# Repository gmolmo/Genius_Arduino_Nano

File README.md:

<h1 align="center"> 🔵🟢 Genius / Simon - Arduino 🟡🔴 </h1>

<div align="center">

</div>

## Descrição do Projeto
O projeto consiste no desenvolvimento do clássico jogo de memória **Genius (ou Simon)** utilizando um **Arduino Nano**. O objetivo do jogo é memorizar e repetir a sequência aleatória de luzes e sons apresentada pelos LEDs e buzzer. É possível selecionar a quantidade de rodadas desejadas e, com o avançar do jogo, o tempo de exibição é diminuído para aumentar a dificuldade.

O desenvolvimento passou pelas etapas de prototipagem em protoboard, soldagem final dos componentes em uma placa perfurada e montagem em um case feito em impressão 3D (feito por membros antigos da **ERUS UFES**).
<div align="center">
  
</div>

## ⚙️ Funcionamento

### Software
O código foi inteiramente programado em **C++** modularizado sob o conceito de **TAD (Tipo Abstrato de Dados)**. A estrutura foi dividida em três arquivos principais:
- `Genius.h`: Contém a definição da classe `Genius`, protótipos de métodos e atributos.
- `Genius.cpp`: Implementação da lógica do jogo, controle de som via buzzer, animações de LEDs (Início, Vitória e Game Over), gerenciamento de estados e leitura dos botões.
- `main.cpp`: Executa o setup e o loop principal com a máquina de estados do jogo.

O programa conta com **3 níveis de dificuldade** selecionáveis pelo botão de controle antes do início da partida, indicados por LEDs dedicados.

### Hardware
- **Arduino Nano**: Microcontrolador responsável pelo processamento da lógica.
- **LEDs Coloridos**: 4 LEDs para a sequência do jogo e 3 LEDs para indicação do nível de dificuldade.
- **Push Buttons**: 4 botões para entrada do jogador e 1 botão para seleção de dificuldade.
- **Buzzer Passivo**: Emite tons em frequências específicas para cada LED e reproduz os efeitos sonoros do jogo.
- **Placa Perfurada**: Circuito soldado para garantir durabilidade e conexões firmes.
- **Case 3D**: Case plástico impresso em 3D para abrigar a eletrônica.

## 🪚 Ferramentas

### C++ / Arduino Framework 
Linguagem utilizada no desenvolvimento de toda a lógica do projeto, aplicando orientação a objetos básica e boa organização estrutural.

### PlatformIO (VS Code)  
Ecossistema utilizado para compilação, gerenciamento de dependências e upload do código diretamente para o Arduino Nano através do Visual Studio Code.

## Instruções

Para compilar e enviar o projeto para o Arduino:

1. Certifique-se de ter o **VS Code** instalado com a extensão do **PlatformIO**.
2. Clone o repositório ou baixe o pacote completo de código.
3. Abra a pasta do projeto no VS Code.
4. Conecte o **Arduino Nano** à porta USB do seu computador.
5. Acesse a aba do **PlatformIO** na barra lateral e clique em **Upload** (ou utilize o atalho do VS Code).

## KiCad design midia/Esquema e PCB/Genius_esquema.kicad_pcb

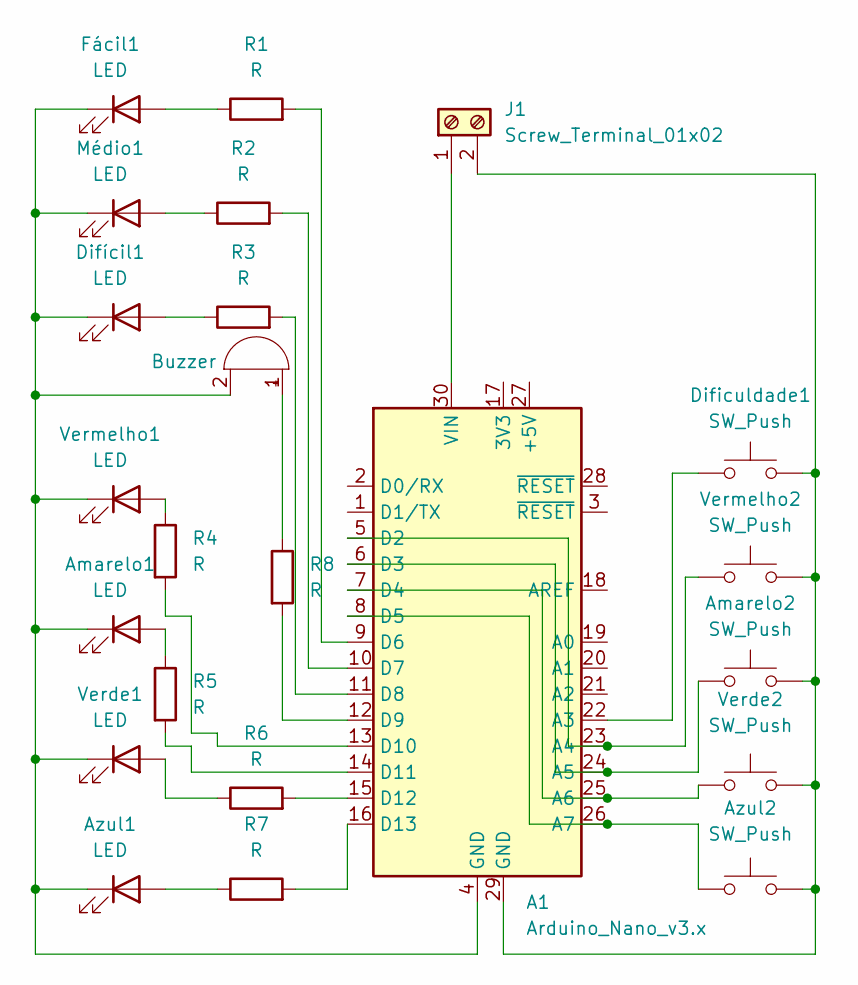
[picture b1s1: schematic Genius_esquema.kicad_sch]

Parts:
A1: Arduino_Nano_v3.x; Arduino_Nano
Amarelo1: LED; LED_D5.0mm
Amarelo2: SW_Push; PinHeader_1x02_P2.54mm_Vertical
Azul1: LED; LED_D5.0mm
Azul2: SW_Push; PinHeader_1x02_P2.54mm_Vertical
BZ1: Buzzer; Buzzer_12x9.5RM7.6
Dificuldade1: SW_Push; PinHeader_1x02_P2.54mm_Vertical
Difícil1: LED; LED_D5.0mm
Fácil1: LED; LED_D5.0mm
J1: Screw_Terminal_01x02; TerminalBlock_Phoenix_MKDS-1,5-2-5.08_1x02_P5.08mm_Horizont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
Médio1: LED; LED_D5.0mm
R1, R2, R3, R4, R5, R6, R7, R8: R; R_Axial_DIN0207_L6.3mm_D2.5mm_P7.62mm_Horizontal
Verde1: LED; LED_D5.0mm
Verde2: SW_Push; PinHeader_1x02_P2.54mm_Vertical
Vermelho1: LED; LED_D5.0mm
Vermelho2: SW_Push; PinHeader_1x02_P2.54mm_Vertical

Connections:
unnamed: A1.22 (A3), Dificuldade1.1
unnamed: A1.5 (D2), A1.23 (A4), Vermelho2.1
unnamed: A1.6 (D3), A1.24 (A5), Amarelo2.1
unnamed: A1.7 (D4), A1.25 (A6), Verde2.1
unnamed: A1.8 (D5), A1.26 (A7), Azul2.1
unnamed: A1.9 (D6), R1.2
unnamed: A1.10 (D7), R2.2
unnamed: A1.11 (D8), R3.2
unnamed: A1.12 (D9), R8.2
unnamed: A1.13 (D10), R4.2
unnamed: A1.14 (D11), R5.2
unnamed: A1.15 (D12), R6.2
unnamed: A1.16 (D13), R7.2
unnamed: A1.30 (VIN), J1.1
unnamed: Amarelo1.2 (A), R5.1
unnamed: A1.4 (GND), Amarelo1.1 (K), Azul1.1 (K), BZ1.2 (-), Difícil1.1 (K), Fácil1.1 (K), Médio1.1 (K), Verde1.1 (K), Vermelho1.1 (K)
unnamed: Azul1.2 (A), R7.1
unnamed: BZ1.1 (+), R8.1
unnamed: Difícil1.2 (A), R3.1
unnamed: Fácil1.2 (A), R1.1
unnamed: A1.29 (GND), Amarelo2.2, Azul2.2, Dificuldade1.2, J1.2, Verde2.2, Vermelho2.2
unnamed: Médio1.2 (A), R2.1
unnamed: R6.1, Verde1.2 (A)
unnamed: R4.1, Vermelho1.2 (A)

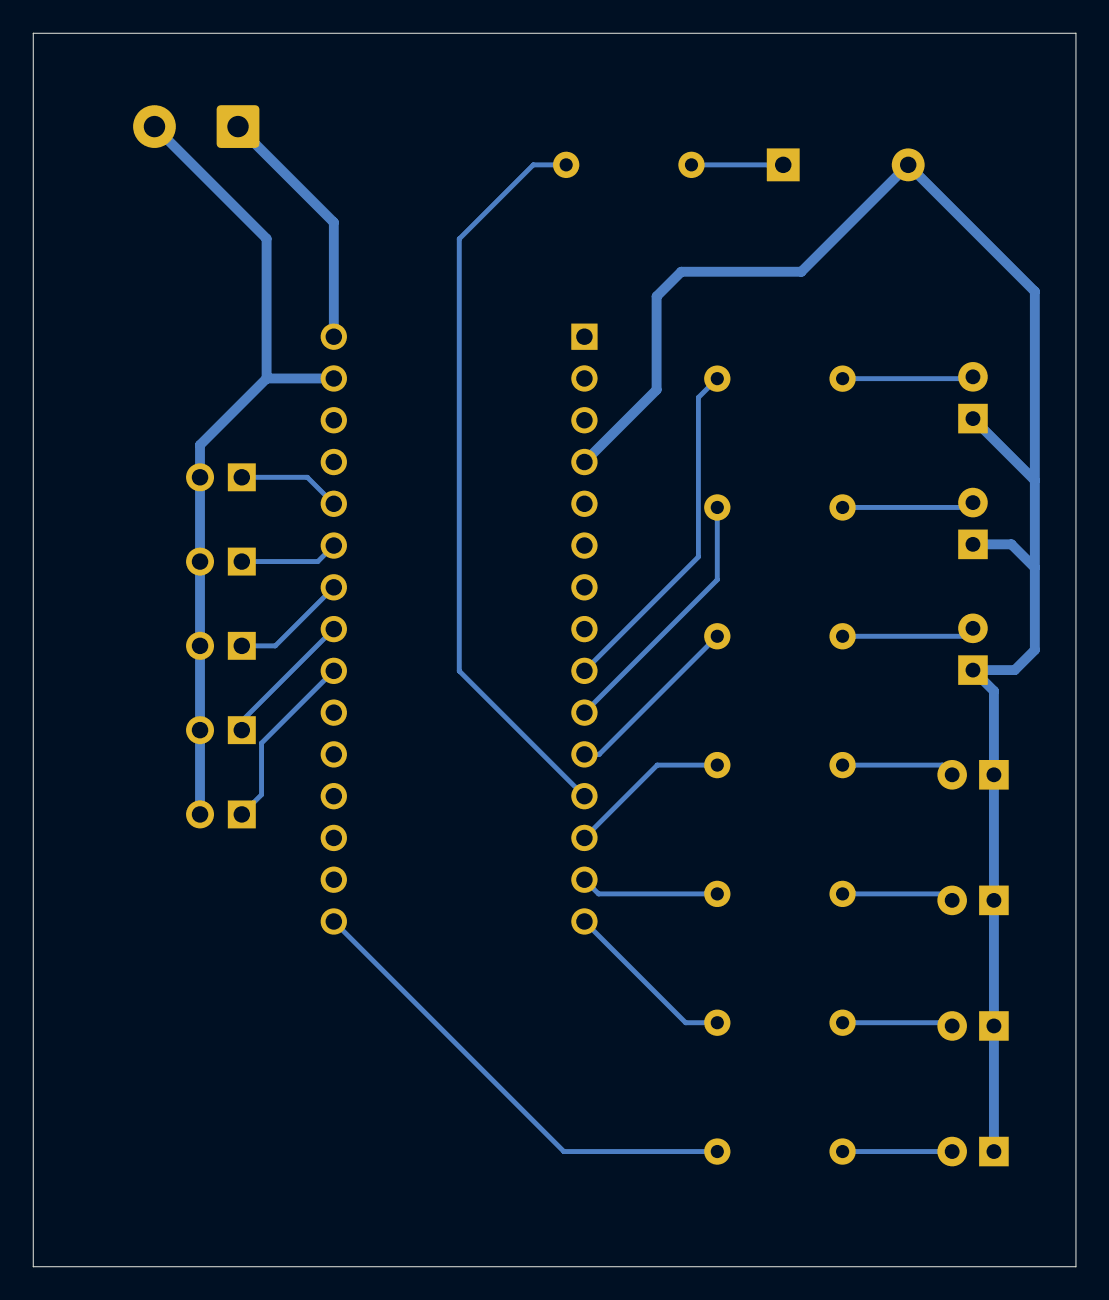
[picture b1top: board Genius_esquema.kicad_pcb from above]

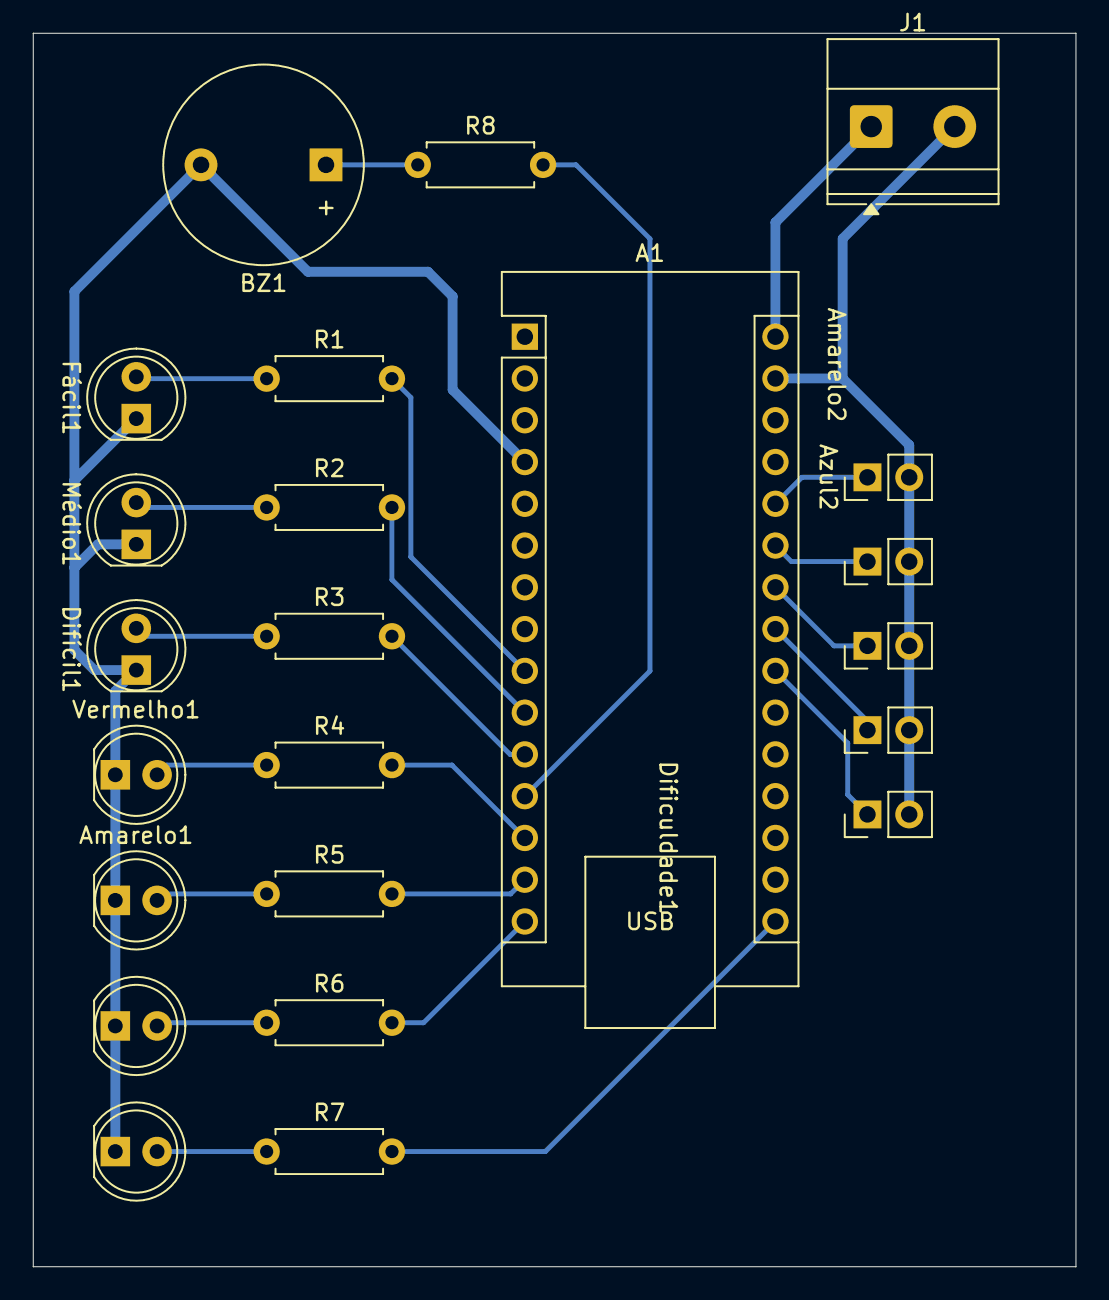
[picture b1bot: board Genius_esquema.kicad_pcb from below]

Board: 2 copper layers, 63.4 x 75.0 mm, 23 parts (23 on the bottom side), 24 nets.
